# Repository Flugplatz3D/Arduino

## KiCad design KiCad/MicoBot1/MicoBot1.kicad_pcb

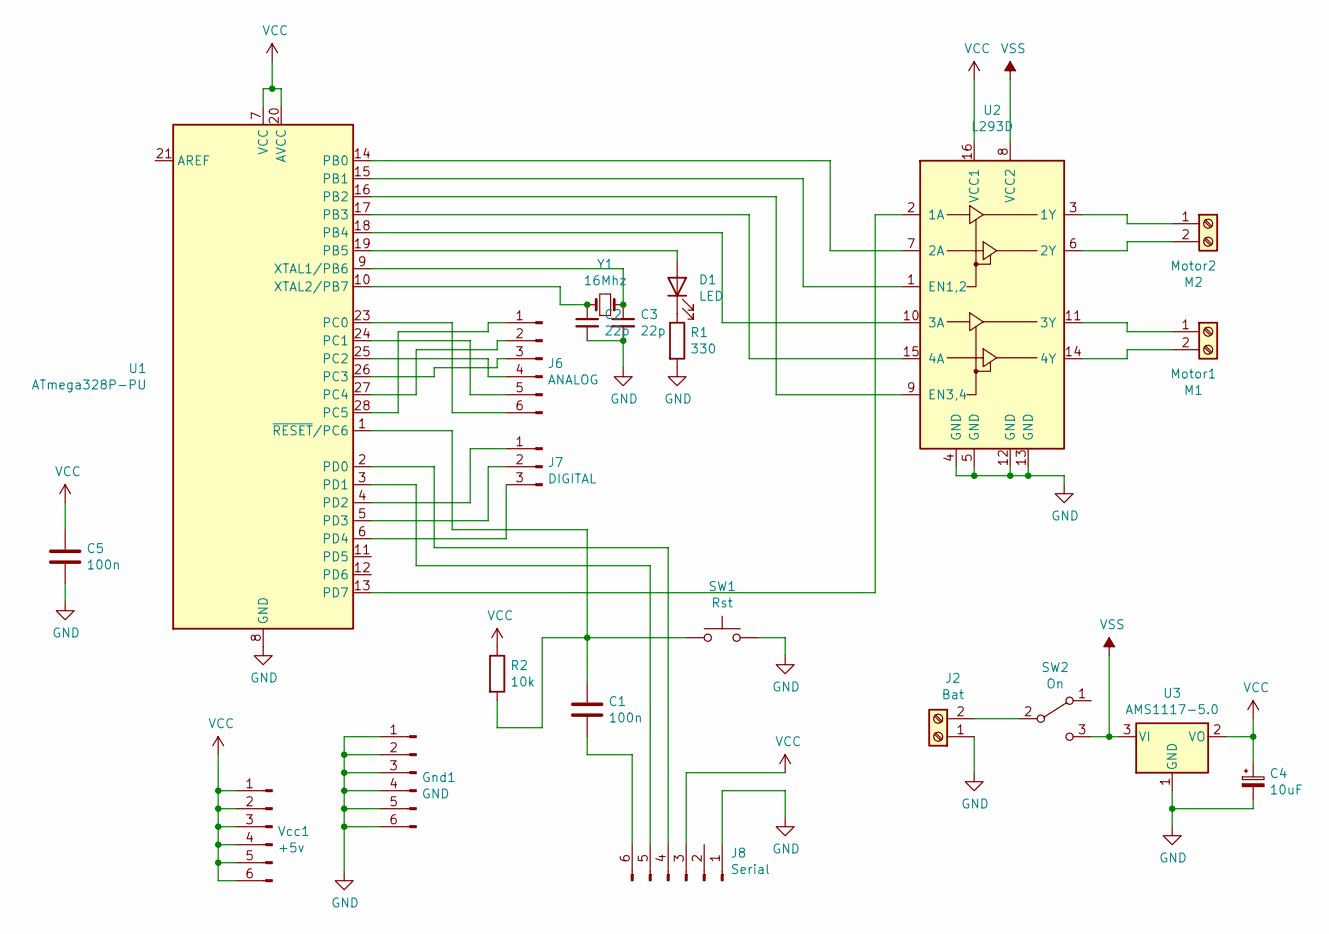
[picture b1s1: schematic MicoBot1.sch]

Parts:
C1: 100n; C_Disc_D4.3mm_W1.9mm_P5.00mm
C2, C3: 22p; C_Disc_D4.3mm_W1.9mm_P5.00mm
C4: 10uF; C_Radial_D5.0mm_H5.0mm_P2.00mm
C5: 100n; C_1206_3216Metric
D1: LED; LED_D3.0mm
Gnd1: GND; PinHeader_1x06_P2.54mm_Vertical
J2: Bat; TerminalBlock_Phoenix_PT-1,5-2-3.5-H_1x02_P3.50mm_Horizontal
J6: ANALOG; PinHeader_1x06_P2.54mm_Vertical
J7: DIGITAL; PinHeader_1x03_P2.54mm_Vertical
J8: Serial; PinHeader_1x06_P2.54mm_Vertical
M1: Motor1; TerminalBlock_Phoenix_PT-1,5-2-3.5-H_1x02_P3.50mm_Horizontal
M2: Motor2; TerminalBlock_Phoenix_PT-1,5-2-3.5-H_1x02_P3.50mm_Horizontal
R1: 330; R_Axial_DIN0204_L3.6mm_D1.6mm_P5.08mm_Horizontal
R2: 10k; R_Axial_DIN0204_L3.6mm_D1.6mm_P5.08mm_Horizontal
SW1: Rst; Pulsador_Cuadrado_6
SW2: On; EG1218
U1: ATmega328P-PU; DIP-28_W7.62mm
U2: L293D; DIP-16_W7.62mm
U3: AMS1117-5.0; SOT-223-3_TabPin2
Vcc1: +5v; PinHeader_1x06_P2.54mm_Vertical
Y1: 16Mhz; Crystal_HC49-4H_Vertical

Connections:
GND: C2.2, C3.2, C4.2, C5.2, Gnd1.1, Gnd1.2, Gnd1.3, Gnd1.4, Gnd1.5, Gnd1.6, J2.1, J8.1, R1.2, SW1.2, U1.8 (GND), U1.22 (GND), U2.4 (GND), U2.5 (GND), U2.12 (GND), U2.13 (GND), U3.1 (GND)
unnamed: C1.1, R2.2, SW1.1, U1.1 (~RESET~/PC6)
unnamed: C1.2, J8.6
unnamed: C2.1, U1.10 (XTAL2/PB7), Y1.1
unnamed: C3.1, U1.9 (XTAL1/PB6), Y1.2
unnamed: D1.1 (K), R1.1
unnamed: D1.2 (A), U1.19 (PB5)
unnamed: J2.2, SW2.2 (B)
unnamed: J6.1, U1.28 (PC5)
unnamed: J6.2, U1.27 (PC4)
unnamed: J6.3, U1.26 (PC3)
unnamed: J6.4, U1.25 (PC2)
unnamed: J6.5, U1.24 (PC1)
unnamed: J6.6, U1.23 (PC0)
unnamed: J7.1, U1.4 (PD2)
unnamed: J7.2, U1.5 (PD3)
unnamed: J7.3, U1.6 (PD4)
unnamed: J8.4, U1.2 (PD0)
unnamed: J8.5, U1.3 (PD1)
unnamed: M1.1, U2.11 (3Y)
unnamed: M1.2, U2.14 (4Y)
unnamed: M2.1, U2.3 (1Y)
unnamed: M2.2, U2.6 (2Y)
unnamed: U1.13 (PD7), U2.2 (1A)
unnamed: U1.14 (PB0), U2.7 (2A)
unnamed: U1.15 (PB1), U2.1 (EN1,2)
unnamed: U1.16 (PB2), U2.9 (EN3,4)
unnamed: U1.17 (PB3), U2.15 (4A)
unnamed: U1.18 (PB4), U2.10 (3A)
VCC: C4.1, C5.1, J8.3, R2.1, U1.7 (VCC), U1.20 (AVCC), U2.16 (VCC1), U3.2 (VO), Vcc1.1, Vcc1.2, Vcc1.3, Vcc1.4, Vcc1.5, Vcc1.6
VSS: SW2.3 (C), U2.8 (VCC2), U3.3 (VI)

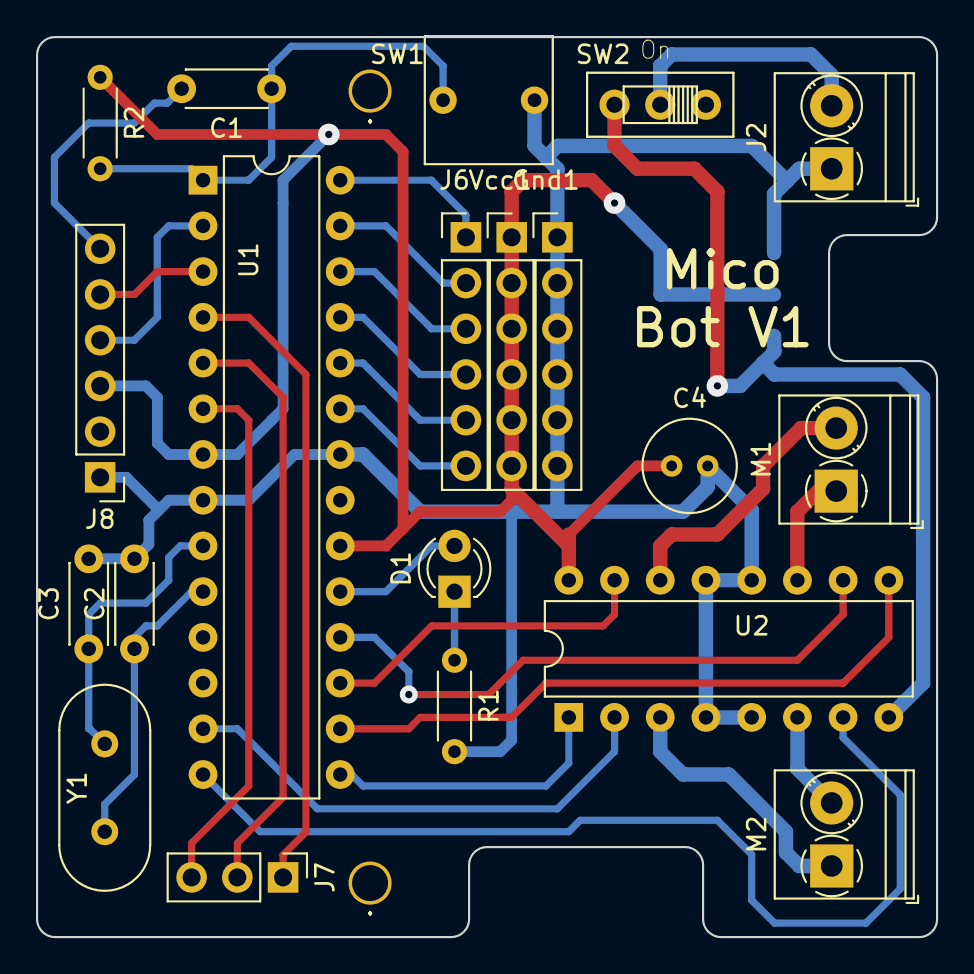
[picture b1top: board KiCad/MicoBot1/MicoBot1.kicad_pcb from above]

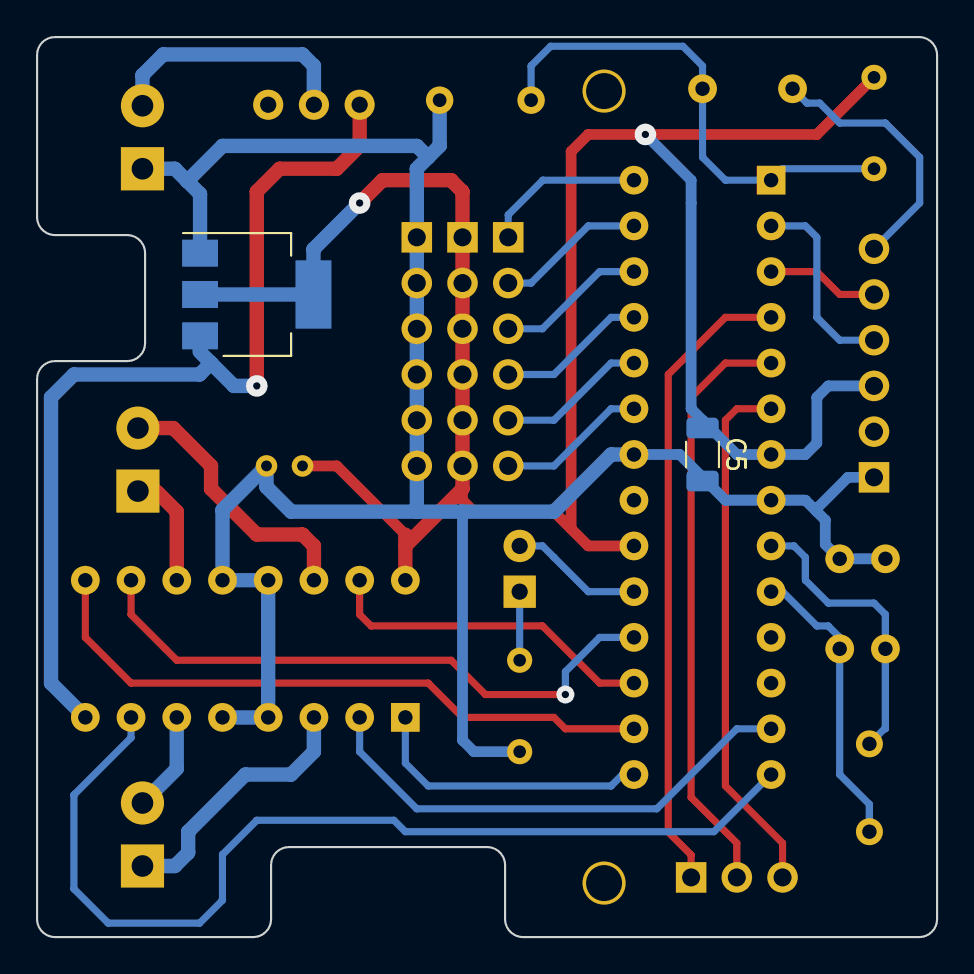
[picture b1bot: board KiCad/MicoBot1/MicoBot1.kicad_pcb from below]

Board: 2 copper layers, 50.0 x 50.0 mm, 24 parts (2 on the bottom side), 31 nets.

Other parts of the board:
., .#2: .; Taladro_2mm

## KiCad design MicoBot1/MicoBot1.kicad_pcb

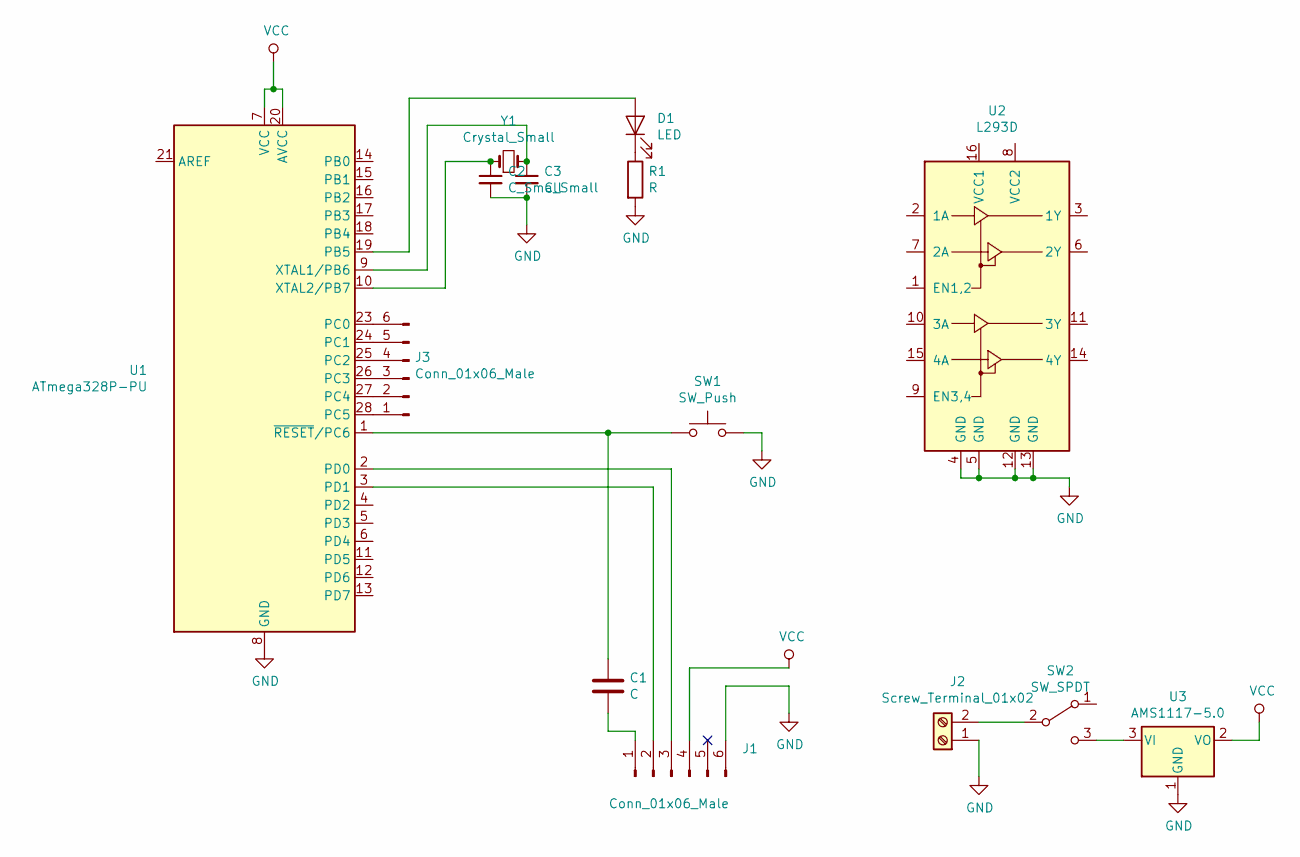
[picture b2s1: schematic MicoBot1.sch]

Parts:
C1: C; C_Disc_D4.3mm_W1.9mm_P5.00mm
C2, C3: C_Small; C_Disc_D4.3mm_W1.9mm_P5.00mm
D1: LED; LED_D3.0mm
J1, J3: Conn_01x06_Male; PinHeader_1x06_P2.54mm_Vertical
J2: Screw_Terminal_01x02; TerminalBlock_MetzConnect_Type059_RT06302HBWC_1x02_P3.50mm_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
R1: R; R_Axial_DIN0204_L3.6mm_D1.6mm_P5.08mm_Horizontal
SW1: SW_Push; Pulsador_Cuadrado_6
SW2: SW_SPDT; EG1218
U1: ATmega328P-PU; DIP-28_W7.62mm
U2: L293D; DIP-16_W7.62mm
U3: AMS1117-5.0; SOT-223-3_TabPin2
Y1: Crystal_Small; Crystal_HC18-U_Vertical

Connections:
GND: C2.2, C3.2, J1.6, J2.1, R1.2, SW1.2, U1.8 (GND), U1.22 (GND), U2.4 (GND), U2.5 (GND), U2.12 (GND), U2.13 (GND), U3.1 (GND)
unnamed: C1.1, SW1.1, U1.1 (~RESET~/PC6)
unnamed: C1.2, J1.1
unnamed: C2.1, U1.10 (XTAL2/PB7), Y1.1
unnamed: C3.1, U1.9 (XTAL1/PB6), Y1.2
unnamed: D1.1 (K), R1.1
unnamed: D1.2 (A), U1.19 (PB5)
unnamed: J1.2, U1.3 (PD1)
unnamed: J1.3, U1.2 (PD0)
unnamed: J2.2, SW2.2 (B)
unnamed: J3.1, U1.28 (PC5)
unnamed: J3.2, U1.27 (PC4)
unnamed: J3.3, U1.26 (PC3)
unnamed: J3.4, U1.25 (PC2)
unnamed: J3.5, U1.24 (PC1)
unnamed: J3.6, U1.23 (PC0)
unnamed: SW2.3 (C), U3.3 (VI)
VCC: J1.4, U1.7 (VCC), U1.20 (AVCC), U3.2 (VO)

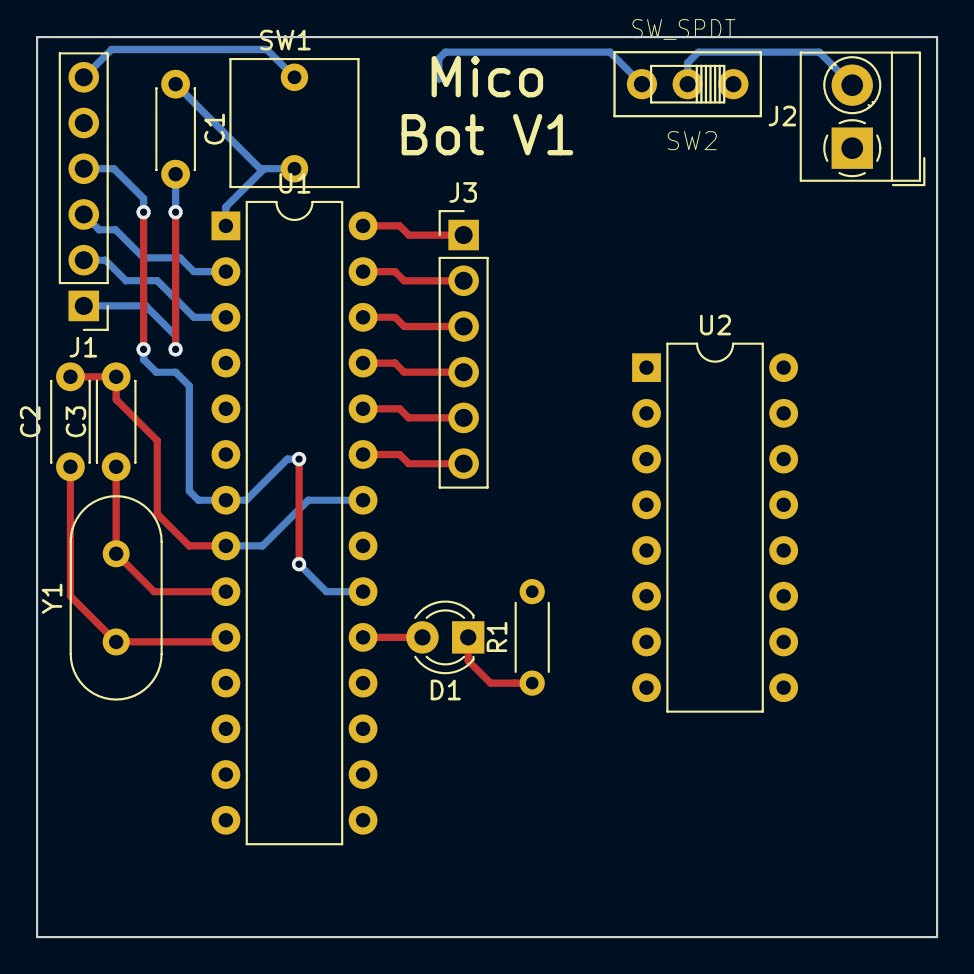
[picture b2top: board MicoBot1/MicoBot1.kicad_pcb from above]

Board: 2 copper layers, 50.0 x 50.0 mm, 14 parts (1 on the bottom side), 18 nets.

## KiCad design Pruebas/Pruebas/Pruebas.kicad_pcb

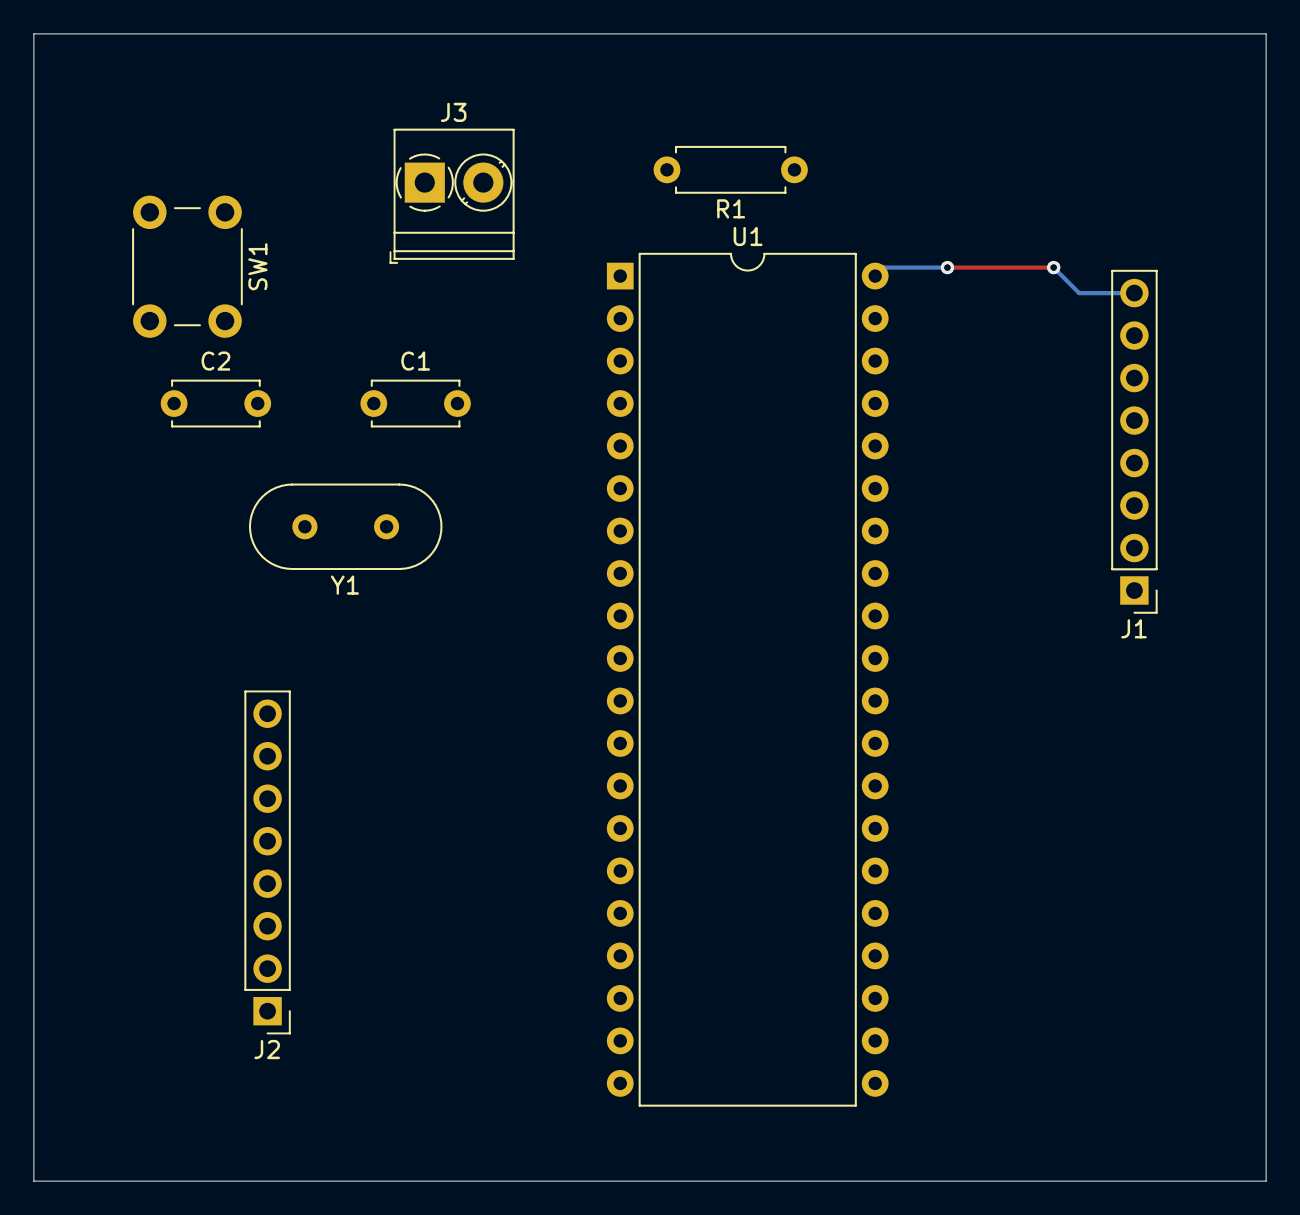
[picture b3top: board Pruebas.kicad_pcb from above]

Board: 2 copper layers, 73.7 x 68.6 mm, 9 parts (0 on the bottom side), 21 nets.

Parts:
C1, C2: C; C_Disc_D5.0mm_W2.5mm_P5.00mm
J1, J2: Conn_01x08_Male; PinHeader_1x08_P2.54mm_Vertical
J3: Screw_Terminal_01x02; TerminalBlock_Phoenix_PT-1,5-2-3.5-H_1x02_P3.50mm_Horizontal
R1: R_Small; R_Axial_DIN0207_L6.3mm_D2.5mm_P7.62mm_Horizontal
SW1: SW_Push; SW_PUSH_6mm_H4.3mm
U1: PIC16F877A-IP; DIP-40_W15.24mm
Y1: Crystal_Small; Crystal_HC49-4H_Vertical

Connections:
GND: C1.2, C2.2, J3.2, SW1.1, U1.12, U1.31
unnamed: C1.1, U1.13, Y1.1
unnamed: C2.1, U1.14, Y1.2
unnamed: J1.1, U1.33
unnamed: J1.2, U1.34
unnamed: J1.3, U1.35
unnamed: J1.4, U1.36
unnamed: J1.5, U1.37
unnamed: J1.6, U1.38
unnamed: J1.7, U1.39
unnamed: J1.8, U1.40
unnamed: J2.1, U1.15
unnamed: J2.2, U1.16
unnamed: J2.3, U1.17
unnamed: J2.4, U1.18
unnamed: J2.5, U1.23
unnamed: J2.6, U1.24
unnamed: J2.7, U1.25
unnamed: J2.8, U1.26
unnamed: R1.2, SW1.2, U1.1
VDD: J3.1, R1.1, U1.11, U1.32
